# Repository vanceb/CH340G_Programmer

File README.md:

# CH340G_Programmer
A programmer to program ESP32 over USB, including the automated reset and programming

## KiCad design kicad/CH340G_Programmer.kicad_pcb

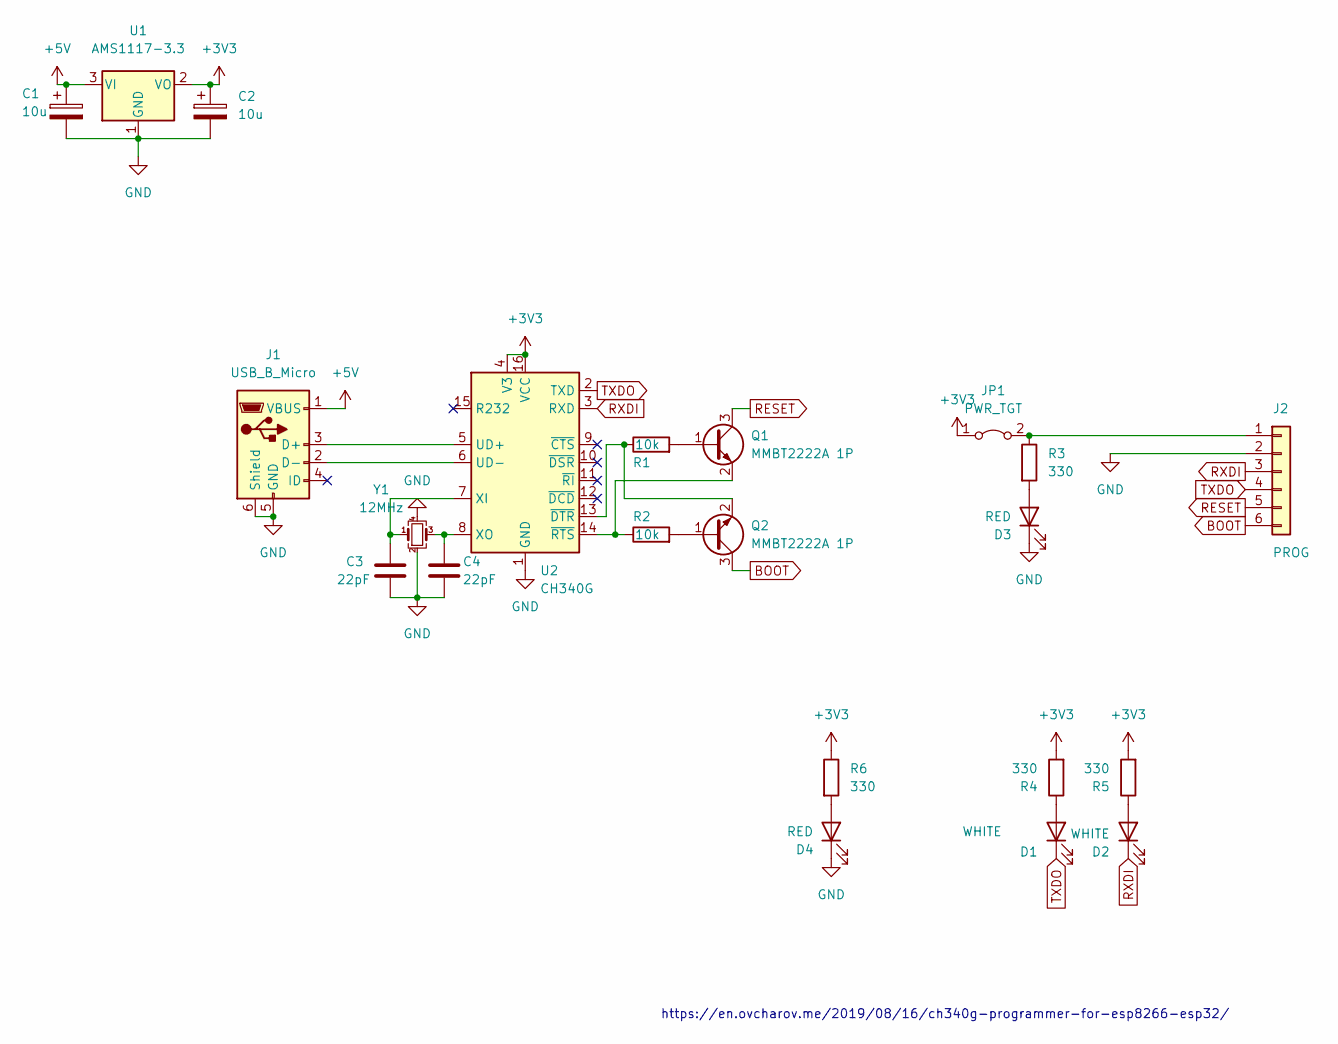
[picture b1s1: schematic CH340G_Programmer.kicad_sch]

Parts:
C1, C2: 10u; CP_EIA-3216-18_Kemet-A; LCSC C7171
C3, C4: 22pF; C_0402_1005Metric; LCSC C1555
D1, D2: WHITE; LED_0603_1608Metric; LCSC C2290
D3, D4: RED; LED_0603_1608Metric; LCSC C2286
J1: USB_B_Micro; XKB_U254_051N_4BH806; LCSC C319170
J2: PROG; PinSocket_1x06_P2.54mm_Vertical
JP1: PWR_TGT; PinHeader_1x02_P2.54mm_Vertical
Q1, Q2: MMBT2222A 1P; SOT-23; LCSC C8512
R1, R2: 10k; R_0603_1608Metric; LCSC C25804
R3, R4, R5, R6: 330; R_0603_1608Metric; LCSC C23138
U1: AMS1117-3.3; SOT-223-3_TabPin2; LCSC C6186
U2: CH340G; SOIC-16_3.9x9.9mm_P1.27mm; LCSC C14267
Y1: 12MHz; Crystal_SMD_3225-4Pin_3.2x2.5mm; LCSC C9002

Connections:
+3V3: C2.1, JP1.1 (A), R4.2, R5.2, R6.1, U1.2 (VO), U2.4 (V3), U2.16 (VCC)
+5V: C1.1, J1.1 (VBUS), U1.3 (VI)
BOOT: J2.6, Q2.3 (C)
GND: C1.2, C2.2, C3.2, C4.2, D3.1 (K), D4.1 (K), J1.5 (GND), J1.6 (Shield), J2.2, U1.1 (GND), U2.1 (GND), Y1.2, Y1.4
unnamed: C3.1, U2.7 (XI), Y1.1
unnamed: C4.1, U2.8 (XO), Y1.3
unnamed: D1.2 (A), R4.1
unnamed: D2.2 (A), R5.1
unnamed: D3.2 (A), R3.2
unnamed: D4.2 (A), R6.2
unnamed: J1.2 (D-), U2.6 (UD-)
unnamed: J1.3 (D+), U2.5 (UD+)
unnamed: J2.1, JP1.2 (B), R3.1
unnamed: Q1.1 (B), R1.2
unnamed: Q1.2 (E), R2.1, U2.14 (~RTS)
unnamed: Q2.1 (B), R2.2
unnamed: Q2.2 (E), R1.1, U2.13 (~DTR)
RESET: J2.5, Q1.3 (C)
RXDI: D2.1 (K), J2.3, U2.3 (RXD)
TXDO: D1.1 (K), J2.4, U2.2 (TXD)

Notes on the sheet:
https://en.ovcharov.me/2019/08/16/ch340g-programmer-for-esp8266-esp32/

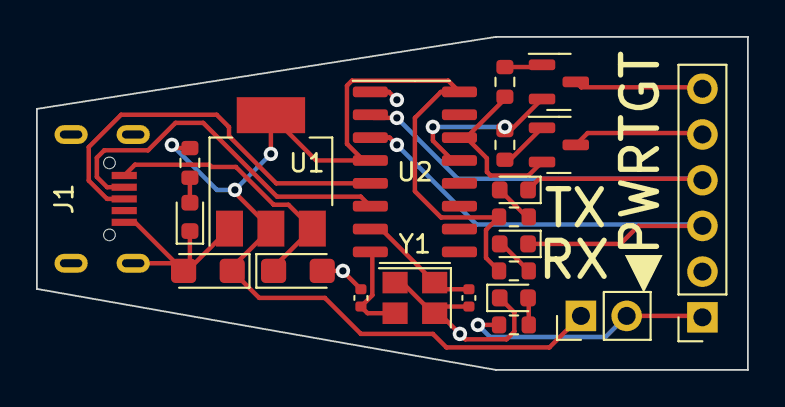
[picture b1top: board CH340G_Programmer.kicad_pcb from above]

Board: 2 copper layers, 39.5 x 18.5 mm, 22 parts (0 on the bottom side), 20 nets.

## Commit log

2022-06-27 Minor improvements to initial design
2022-06-27 Tidy prior to release
2022-06-27 Initial production output
2022-06-27 Added jumper to allow choice of power to target or not. Also added LED to indicate additional power rail
2022-06-27 Corrected USB MicroB footprint to match the schematic - Was missing Pin6 (Shell)
2022-06-27 Updated gerbers after last change
2022-07-01 Updated .gitignore to track BOM and POS files needed for fabrication
2024-10-01 Added gerbers for last release
